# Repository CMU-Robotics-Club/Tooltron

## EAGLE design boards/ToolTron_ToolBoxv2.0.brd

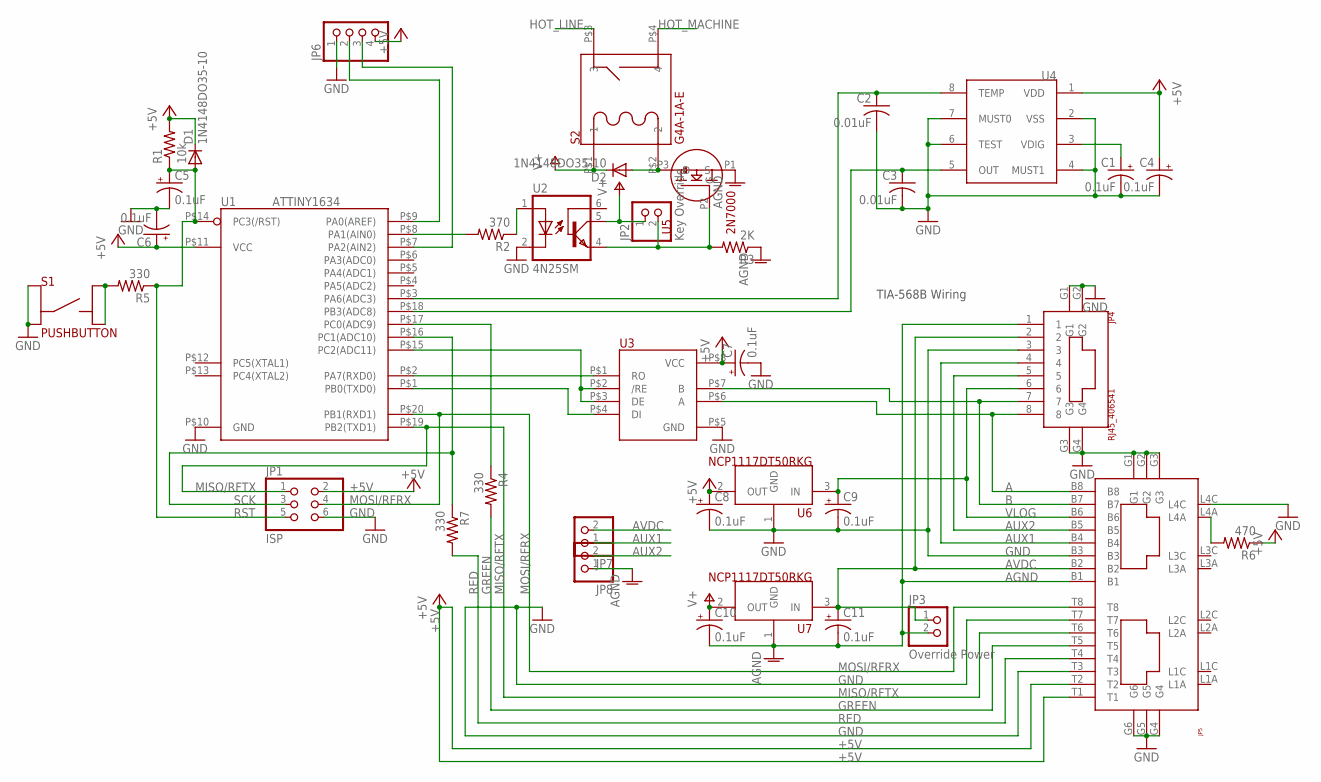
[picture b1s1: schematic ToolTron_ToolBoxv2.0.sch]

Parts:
C1, C4, C10, C11: 0.1uF; UD-4X5,8_NICHICON
C2, C3: 0.01uF; C0805
C5, C6, C7, C8, C9: 0.1uF; E2-5
D1, D2: 1N4148DO35-10; DO35-10
JP1: ISP; 2X03
JP2: Key Override; 1X02_OVAL
JP3: Override Power; 1X02_OVAL
JP4: RJ45_406541; 1-406541-1
JP5: 2XRJ45_RJSAE538X02X; RJSAE538X02X
JP6: HEADER-1X4ROUND; 1X04_ROUND
JP7, JP8: HEADER-1X2ROUND; 1X02_ROUND
R1: 10k; 0207/10
R2: 370; 0207/10
R3: 2K; 0207/10
R4, R5, R7: 330; 0207/10
R6: 470; 0207/10
S1: PUSHBUTTON; FSM4JH
S2: G4A-1A-E
U1: ATTINY1634; SOIC-20
U2: 4N25SM; DIL6-SMD; MPN 4N25SM
U3: MAX13082E; SOIC-8
U4: MLX91206; SOIC-8
U5: 2N7000; TO-92
U6, U7: NCP1117DT50RKG; DPAK

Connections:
+5V: C4.+, C6.+, C7.+, C8.+, D1.C, JP1.2, JP5.T1, JP5.T2, JP6.4, R1.2, R6.1, U1.P$11 (VCC), U3.P$8 (VCC), U4.1 (VDD), U6.2 (OUT)
A: JP4.8, JP5.B8, U3.P$6 (A)
AGND: C10.-, C11.-, JP3.2, JP4.1, JP5.B1, JP8.1, R3.1, U5.P1 (S), U7.1 (GND)
AUX1: JP4.4, JP5.B4, JP7.1
AUX2: JP4.5, JP5.B5, JP8.2
AVDC: C11.+, JP3.1, JP4.2, JP5.B2, JP7.2, U7.3 (IN)
B: JP4.7, JP5.B7, U3.P$7 (B)
DI: U1.P$1 (PB0(TXD0)), U3.P$4 (DI)
EN: U1.P$15 (PC2(ADC11)), U3.P$2 (/RE), U3.P$3 (DE)
GND: C1.-, C2.2, C3.2, C4.-, C5.-, C6.-, C7.-, C8.-, C9.-, JP1.6, JP4.3, JP4.G1, JP4.G2, JP4.G3, JP4.G4, JP5.B3, JP5.G1, JP5.G2, JP5.G3, JP5.G4, JP5.G5, JP5.G6, JP5.L4C, JP5.T3, JP5.T7, JP6.1, S1.1, S1.2, U1.P$10 (GND), U2.2 (C), U3.P$5 (GND), U4.2 (VSS), U4.4 (MUST1), U4.6 (TEST), U4.7 (MUST0), U6.1 (GND)
GREEN: JP5.T5, R4.2
HOT_LINE: S2.P$3 (3)
HOT_MACHINE: S2.P$4 (4)
MISO/RFTX: JP1.1, JP5.T6, U1.P$19 (PB2(TXD1))
MOSI/RFRX: JP1.4, JP5.T8, U1.P$20 (PB1(RXD1))
unnamed: D2.A, S2.P$2 (2), U5.P3 (D)
unnamed: R5.2, S1.3, S1.4
unnamed: C3.1, U1.P$18 (PB3(ADC8)), U4.5 (OUT)
unnamed: C1.+, U4.3 (VDIG)
unnamed: C2.1, U1.P$3 (PA6(ADC3)), U4.8 (TEMP)
unnamed: R2.2, U1.P$8 (PA1(AIN0))
unnamed: R2.1, U2.1 (A)
unnamed: JP2.2, R3.2, U2.4 (EMI), U5.P2 (G)
unnamed: JP5.L4A, R6.2
unnamed: R4.1, U1.P$17 (PC0(ADC9))
PA0: JP6.2, U1.P$9 (PA0(AREF))
PA2: JP6.3, U1.P$7 (PA2(AIN2))
RED: JP5.T4, R7.2
RO: U1.P$2 (PA7(RXD0)), U3.P$1 (RO)
RST: C5.+, D1.A, JP1.5, R1.1, R5.1, U1.P$14 (PC3(/RST))
SCK: JP1.3, R7.1, U1.P$16 (PC1(ADC10))
V+: C10.+, D2.C, JP2.1, S2.P$1 (1), U2.5 (COL), U7.2 (OUT)
VLOG: C9.+, JP4.6, JP5.B6, U6.3 (IN)

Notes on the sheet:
TIA-568B Wiring

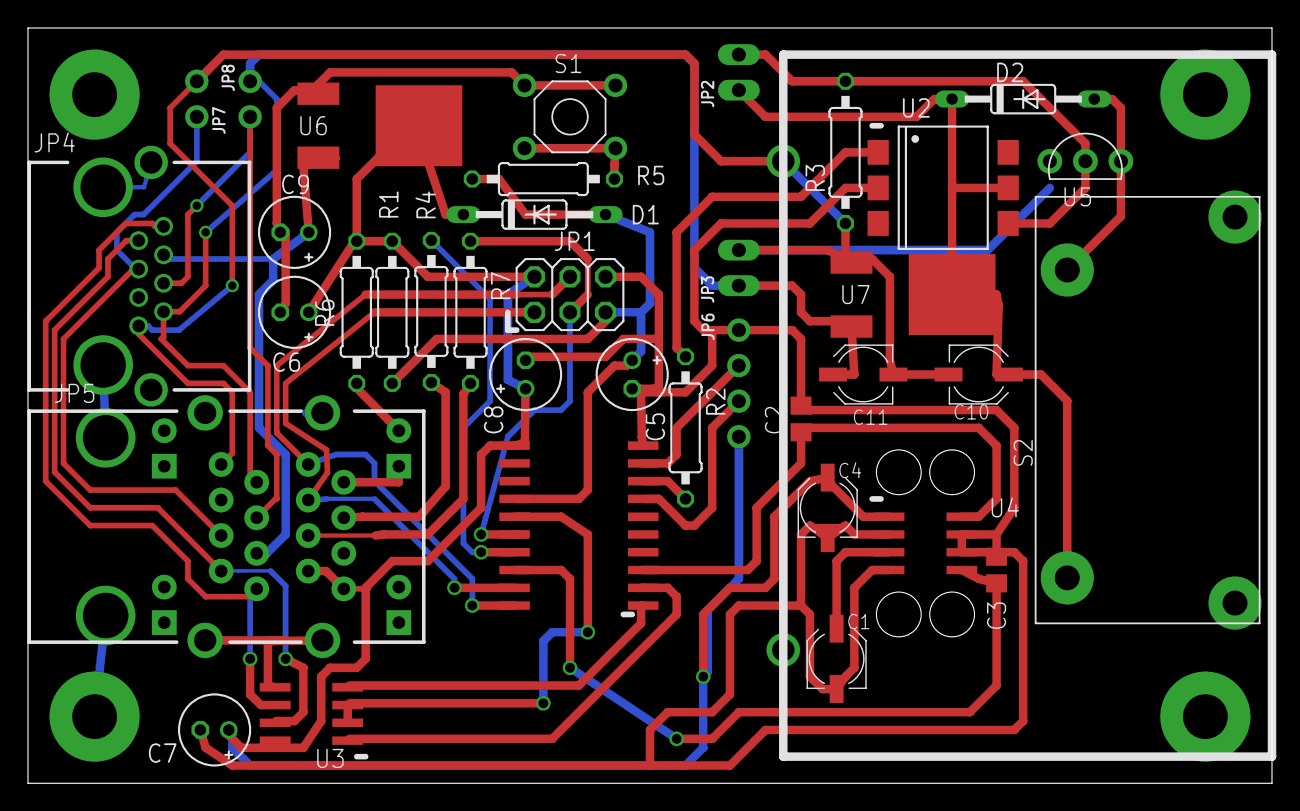
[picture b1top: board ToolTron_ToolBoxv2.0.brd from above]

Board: 2 copper layers, 88.9 x 54.0 mm, 37 parts (0 on the bottom side), 31 nets.

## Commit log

2012-11-10 Initial commit of freemodbus and code by Anson and me
2012-11-10 Moved rfid functions into their own file
2012-11-10 Added ability to read input registers
2012-11-10 Got rid of annoying warning about usTimerOCRBDelta
2012-11-10 Added ATtiny1634 write to UCSRC in portserial.c
2012-11-12 Moved toolbox code into its own directory
2012-11-12 Added script to read from rfid reader
2012-11-13 Initial commit of mainbox code.
2012-11-14 Added capability to read/write coils to toolbox
2012-11-15 Renamed tool_get_user to tool_read_user
2012-11-15 Added actual control of tool
2012-11-15 Made some changes to the tool state machine
2012-11-18 Fixed problem with high error in serial clock
2012-11-18 Deleted accidently commited vim swap file
2012-11-18 Removed superfluous printf in rfid read script
2012-11-18 Changed register/coil addresses to be 1 indexed
2012-11-18 Fixed U2X1 being set in the wrong control register
2012-11-18 Added RTS_ENABLE to Makefile
    Also added UL to end of F_CPU
2012-11-18 Various fixes to tool main.c
    - Input register callback no longer copies current_user to reg_buf
    prematurely, and then write the uninitialized serno into reg_buf (?!)
    - tool_disable was missing a ~
    - Updated coil read/write to use new 1 indexed addresses
2012-11-18 Added printing the response timeout, and other fixes
    - Fixed using SLAVE_ADDR instead of tool->address
    - Replaced read_registers with read_input_registers
2012-11-19 Added serial_flush
2012-11-21 Added LED header, and some rfid debugging
2012-11-21 Changed F_CPU to 8MHz instead of 1MHz
2012-11-27 Eradicated use of signed chars in serial *d'oh*
2012-11-27 Revert "Removed superfluous printf in rfid read script"
    This reverts commit e66d0e5c23eaaf3db53409d05beb0e1fcdbe1610.
2012-11-28 Fixed compile errors; finished converting char -> uint8_t
2012-11-29 Added LED blinking, and other fixes
2012-12-01 Fixes. It tooltrons at a basic level now.
2012-12-02 Made rfid.c more robust against false negatives
    Also changed LED code to be more generally usable, and changed mainbox
    to grant access to a particular user id instead of randomly choosing
2012-12-03 Fixed timer error correction
2012-12-03 Added tool state TS_DENY, with red LED until card is removed
2012-12-03 Added c program for reading from rfid reader on computer
2012-12-03 Tool stops waiting for access response if id is removed
2012-12-11 Added current sensing to toolbox
2012-12-12 initial commit of tooltron boards
2012-12-13 Moved timing to time.c, and increased period of rfid polling
2012-12-13 Changed read util to flush input and wait for reads to complete
2012-12-13 Added flushing before write to rfid reader
    And other various fixes and changes, which I don't remember. Changed
    rfid reading to read every tick, but only try writing if enough ticks
    have passed.
2012-12-27 initial commit of virtual python enviornment and django project. this should create a fully reproduceable devolopment enviornment. for info see www.jeffknupp.com/blog/2012/02/09/starting-a-django-pro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
2012-12-27 added south for database migration
2012-12-28 created new app roboclub crm. I will be working on user authentication and the user model
2012-12-31 Updated user model
2013-01-03 Finished defining models. Also added function to create RoboUser instances. Also modified settings to look for RoboUser as the default user class.
2013-01-04 fixed a couple errors in the models.py. Then preformed a migration.
2013-01-05 added __unicode__ functions to models
2013-01-05 fixed issue with models for form validation. Allowed fields to be blank that should be able to be blank.
2013-01-05 fixed not allowing null for db for dates
2013-01-05 still trying to fix null
2013-01-06 added admin interface.
2013-01-06 preformed database migrations to fix null issues
2013-01-12 customizing user admin
2013-01-19 Added query.c for queries from database web interface
2013-01-20 added first attempt to do machine authentication
2013-01-20 changed model to allow for hex rfid cards
2013-01-20 working on urls. views not working right
2013-01-21 added tool authentication system. It works!
2013-01-21 updated urls page.
2013-01-21 Added getopt for inputting serial device and CRM server
2013-01-27 updated boards to include holes.
2013-01-27 jeff made changes to model and added migrations
2013-01-28 Made errors less noisy
    If it can't connect to a tool, it will print an error once, and then
    print another message when it is able to reconnect.
2013-01-28 Moved tool address to Makefile
2013-01-30 mainbox now prints error on 404 or 500 from server
2013-02-03 Fixed annoying warnings about avr/signal.h
2013-02-10 Untested current RMS calculation
    It's not actually RMS, it's variance. Same general idea.
2013-02-10 Switch ADC to timer 1 because timer 0 was taken. Oops.
2013-02-18 Fixed overflow in current calculation
2013-02-28 Fixed timing in current sensing
    The ADC interrupt didn't clear the TIFR timer interrupt flag, which
    means the ADC wasn't triggered again on the next compare match.
2013-03-01 Fixed another overflow bug and removed isqrt
2013-03-08 Removed virtualenv and added requirements.txt in its place
    Now each developer can have their own virtual environment built from
    requirements.txt, without the annoying path problems that come from the
    environment being under source control
2013-03-08 Added some scripts for working with virtualenv and running the server
2013-03-08 Removed a bunch of .pyc files
2013-03-12 Added query_add_event to mainbox code
2013-03-20 Fixed curl SSL queries failing and queue bug
2013-03-20 Added username/password to add_event query
2013-03-23 Event submissions from ./tooltron tested and working
2013-03-23 Added add_card_event view and made some minor changes to models
2013-03-23 Fixed Add User page error
2013-03-23 Removed migrations from repo
2013-03-23 Added environment setup to wsgi.py for usage with apache
2013-03-24 Adding program_tool script so we remember how to set tool id
2013-03-24 Fixed missing import in views.py
2013-03-24 query.c has optional debug output for /add_card_event
2013-03-24 Removed rfid_restart flag
    This way the AVR will always repoll the rfid reader after the timeout,
    so hopefully it will never hang. Who knows?
2013-04-01 Removed some of the fields on the add user admin page
2013-04-14 Adding rfid-web
    The javascript will query the rfid reader (using main.c, set up on
    tooltron.roboclub.org with CGI) and insert it into a form.
2013-05-05 Changed URLs to match actual server
2013-05-05 Added new logging functions which inject timestamps
2013-05-13 Major changes to mainbox code.
    -Added local cache for RFID -> tool permissions
    -Queries new page /crm/roboauth/%08x, which gives bitmask of all tool
    permissions instead of just one
    -Added pid file at /var/run/tooltron.pid
    -Now must be run as "tooltron run" and also has "tooltron refresh" and
    "tooltron clear" which send signals to the pid in the pid file
2013-05-13 Added new view roboauthall
    It returns bitmask of all tool permissions for a given user
2013-06-09 Added stop command and fixed pid file deletion
2013-06-09 Minor typo
2013-09-19 Added automatic subscription to roboclub-gb on user creation
2013-10-06 Simplified read_file
2013-10-06 Fixed build warnings from last commit
2013-10-06 Added LRU eviction to cache. Not tested yet.
2014-02-13 Implemented code for new RFID readers
    It's not fully working yet. When the checksum is enabled, it ignores all
    responses. Also, it no longer recognizes a missing card.
2014-02-13 Fixed event queue bug
2014-02-13 Added clarifying comment for code that confused me
    TODO document all this lol
2014-02-13 Removed pid file necessity
    Still uses it if running as root, but otherwise doesn't bother. Should
    be a bit easier for local testing.
2014-02-13 Fixed card removal detection
    Also switched from using seek command to select command with the reader.
    Select returns a result immediately, rather than seek which first
    returns an "in progress" error then later returns the card (as far as I
    can tell).
2014-04-13 Fixed exception in event add page
2014-04-14 Fixed problems with previous fix
2014-04-20 Adding init script for mainbox installation
2014-04-20 Fixed a few issues setting up tooltron on Marvin
2014-04-25 Shorted modbus timeout
2014-10-18 Added shutoff when current is sensed when enabling tool
    Also made a number of fixes to current sensing, which was quite broken.
2014-10-31 Removed dead crm code no longer part of Tooltron project.
2015-03-09 Removed 'cache' code.
2015-03-12 Git repository now up-to-date with code in production.
2015-03-15 Fixed URL construction with tool_id bug.
2015-03-15 Only attempt to send add_card_event once.
2015-03-15 Use cache on network failure. Update on every successful server request.
2015-04-03 Server parameter now must include 'http:' or 'https:' prefix. Tools quried from server on startup for consistancy between server and daemon.
2015-04-03 Removed dead 'rfid-web' folder.
2015-04-03 Tool 'powered' field support.
2015-04-03 Tool timeout changed from 150 to 300.

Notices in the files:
parts and their libraries:
microbuilder: This work is placed in the public domain, and may be freely used for commercial and non-commercial work with the following conditions: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
